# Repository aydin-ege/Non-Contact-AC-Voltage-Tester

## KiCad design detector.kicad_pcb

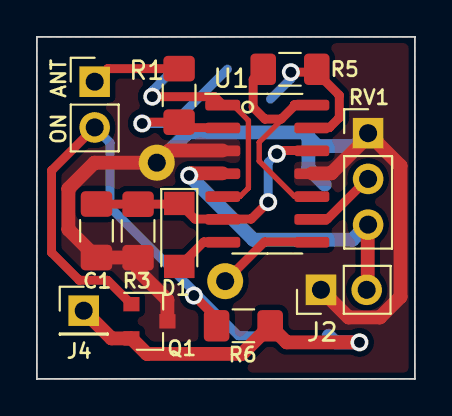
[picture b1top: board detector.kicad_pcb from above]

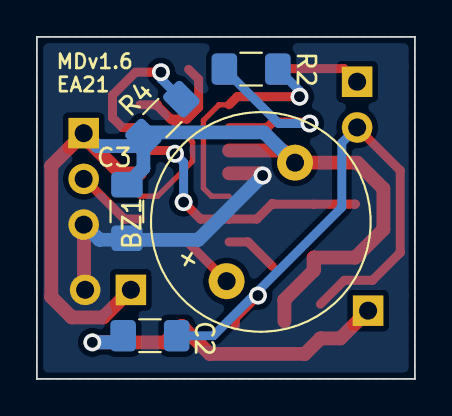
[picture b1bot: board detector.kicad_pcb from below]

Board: 2 copper layers, 21.0 x 19.0 mm, 17 parts (5 on the bottom side), 13 nets.

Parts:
BZ1: Buzzer; Buzzer_12x9.5RM7.6
C1, C2, C3: C; C_1206_3216Metric_Pad1.42x1.75mm_HandSolder
D1: D; D_MiniMELF
J1, J2: PWR; PinHeader_1x02_P2.54mm_Vertical
J4: N_BAT; PinHeader_1x01_P2.54mm_Vertical
Q1: Q_NMOS_GSD; SOT-23
R1, R2, R3, R4, R5, R6: R_US; R_1206_3216Metric_Pad1.42x1.75mm_HandSolder
RV1: R_POT; PinHeader_1x03_P2.54mm_Vertical
U1: LMV324; SOIC-14_3.9x8.7mm_P1.27mm

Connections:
+3V3: C3.1, J2.2, RV1.3, U1.4
-BATT: C2.2, J4.1, Q1.2, R6.1
GND: BZ1.2, C1.2, C3.2, J2.1, Q1.3, R3.2, R4.2, RV1.1, U1.3, U1.11
unnamed: BZ1.1, U1.8
unnamed: C1.1, D1.1, R3.1, U1.6, U1.12
unnamed: C2.1, J1.2, Q1.1, R6.2
unnamed: D1.2, U1.7
unnamed: J1.1, R1.2
unnamed: R1.1, R2.2, U1.2
unnamed: R2.1, U1.1, U1.5
unnamed: R4.1, R5.2, U1.13
unnamed: R5.1, U1.10, U1.14
unnamed: RV1.2, U1.9

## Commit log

2021-10-26 Create LICENSE
